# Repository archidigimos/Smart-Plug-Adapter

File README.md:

# Smart-Plug-Adapter
Converts any normal power outlet into smart power outlet when plugged into it. WiFi enabled, can be controlled through Android application or Web Application.

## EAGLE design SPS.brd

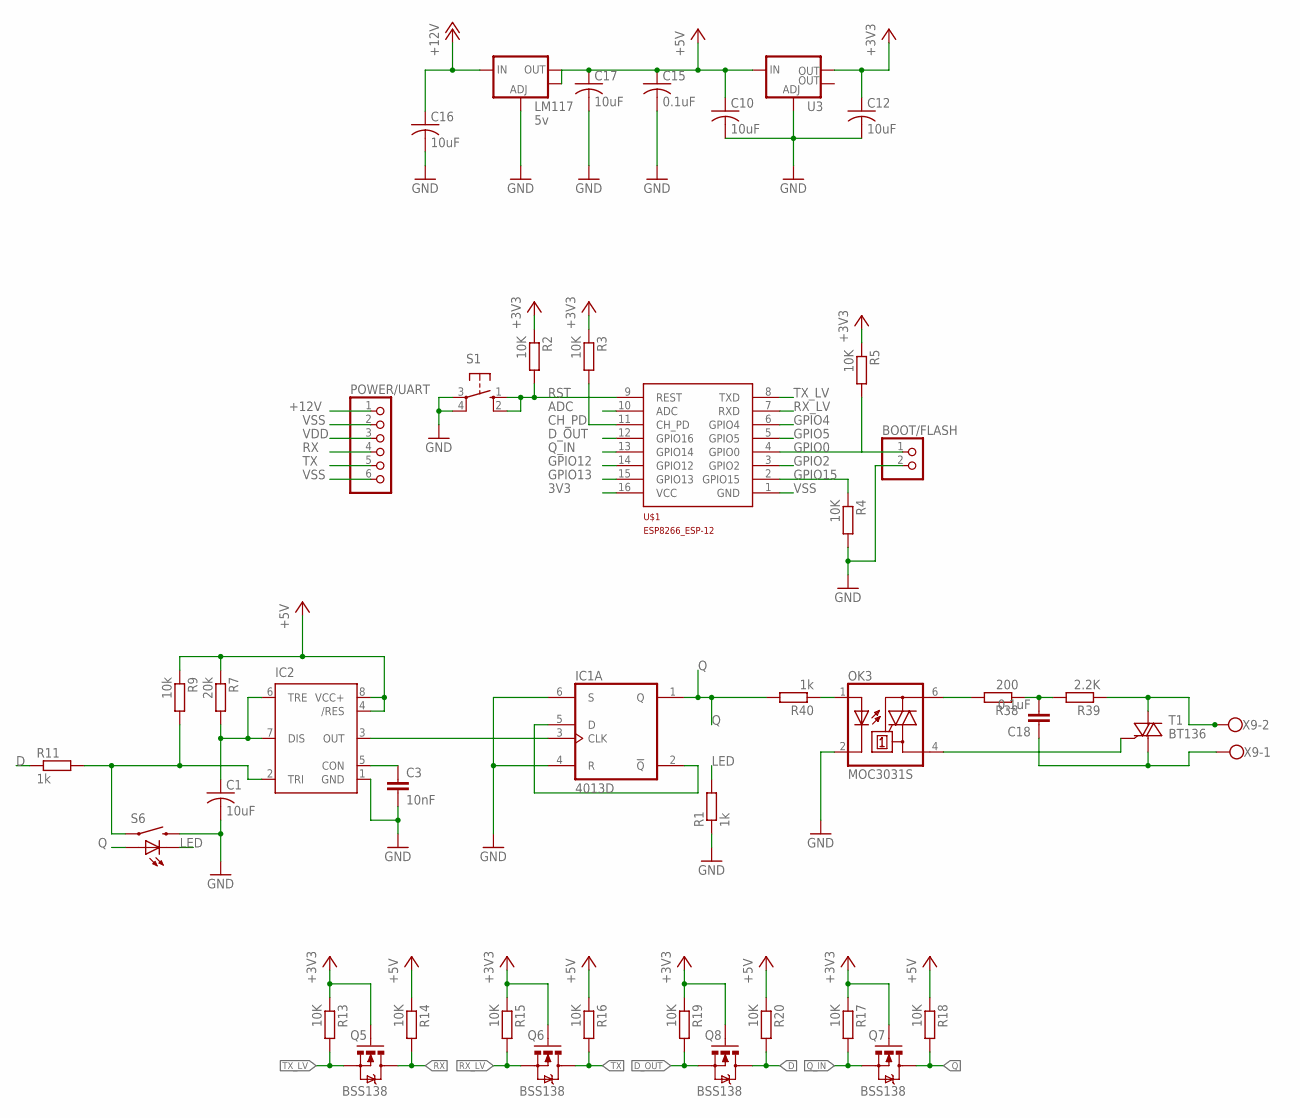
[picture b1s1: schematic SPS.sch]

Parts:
BOOT/FLASH: PINHD-1X2; 1X02
C1, C10, C12: 10uF; C1206
C3: 10nF; C1206
C15: 0.1uF; C0805
C16, C17: 10uF; C0805
C18: 0.1uF; C050-050X075
IC1: 4013D; SO14
IC2: NE555D; SO08
LM117: 5v; SOT223
OK3: MOC3031S; DIL6-SMD
POWER/UART: PINHD-1X6; 1X06
Q5, Q6, Q7, Q8: BSS138; SOT23-3
R1, R11, R40: 1k; R1206
R2, R3, R4, R5, R13, R14, R15, R16, R17, R18, R19, R20: 10K; R1206
R7: 20k; R1206
R9: 10k; R1206
R38: 200; 0414/15
R39: 2.2K; 0414/15
S1: 10-XX; B3F-10XX
S6: SWITCH-MOMENTARY-LEDPTH; TACTILE-PTH-LED-12MM
T1: BT136; TO220AB
U3: V_REG_LM1117SOT223; SOT223
U$1: ESP8266_ESP-12; ESP8266-ESP12
X9: W237-102

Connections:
3V3: C12.1, Q5.1 (G), Q6.1 (G), Q7.1 (G), Q8.1 (G), R2.1, R3.1, R5.1, R13.1, R15.1, R17.1, R19.1, U3.2 (OUT), U$1.16 (VCC)
+12V: C16.1, LM117.3 (IN), POWER/UART.1
ADC: U$1.10 (ADC)
CH_PD: R3.2, U$1.11 (CH_PD)
D: Q8.3 (D), R11.1, R20.2
D_OUT: Q8.2 (S), R19.2, U$1.12 (GPIO16)
GPIO0: BOOT/FLASH.1, R5.2, U$1.4 (GPIO0)
GPIO2: U$1.3 (GPIO2)
GPIO4: U$1.6 (GPIO4)
GPIO5: U$1.5 (GPIO5)
GPIO12: U$1.14 (GPIO12)
GPIO13: U$1.15 (GPIO13)
GPIO15: R4.1, U$1.2 (GPIO15)
LED: R1.2, S6.C
unnamed: OK3.6 (A2), R38.2
unnamed: C18.1, T1.1 (A1), X9.1
unnamed: IC1.2 (!Q), IC1.5 (D)
unnamed: IC1.3 (CLK), IC2.3 (OUT)
unnamed: C1.1, IC2.6 (TRE), IC2.7 (DIS), R7.2
unnamed: C3.1, IC2.5 (CON)
unnamed: IC2.2 (TRI), R9.2, R11.2, S6.4 (1)
unnamed: R39.1, T1.2 (A2), X9.2
unnamed: OK3.4 (A1), T1.3 (G)
unnamed: C18.2, R38.1, R39.2
unnamed: OK3.1 (A), R40.1
Q: IC1.1 (Q), Q7.3 (D), R18.2, R40.2, S6.A
Q_IN: Q7.2 (S), R17.2, U$1.13 (GPIO14)
RST: R2.2, S1.1 (S), S1.2 (S1), U$1.9 (REST)
RX: POWER/UART.4, Q5.3 (D), R14.2
RX_LV: Q6.2 (S), R15.2, U$1.7 (RXD)
TX: POWER/UART.5, Q6.3 (D), R16.2
TX_LV: Q5.2 (S), R13.2, U$1.8 (TXD)
VDD: C10.1, C15.1, C17.1, IC1.14 (VDD), IC2.4 (/RES), IC2.8 (VCC+), LM117.2 (OUT), LM117.4 (OUT), POWER/UART.3, R7.1, R9.1, R14.1, R16.1, R18.1, R20.1, U3.3 (IN)
VSS: BOOT/FLASH.2, C1.2, C3.2, C10.2, C12.2, C15.2, C16.2, C17.2, IC1.4 (R), IC1.6 (S), IC1.7 (VSS), IC2.1 (GND), LM117.1 (ADJ), OK3.2 (C), POWER/UART.2, POWER/UART.6, R1.1, R4.2, S1.3, S1.4 (P1), S6.2, U3.1 (ADJ), U$1.1 (GND)

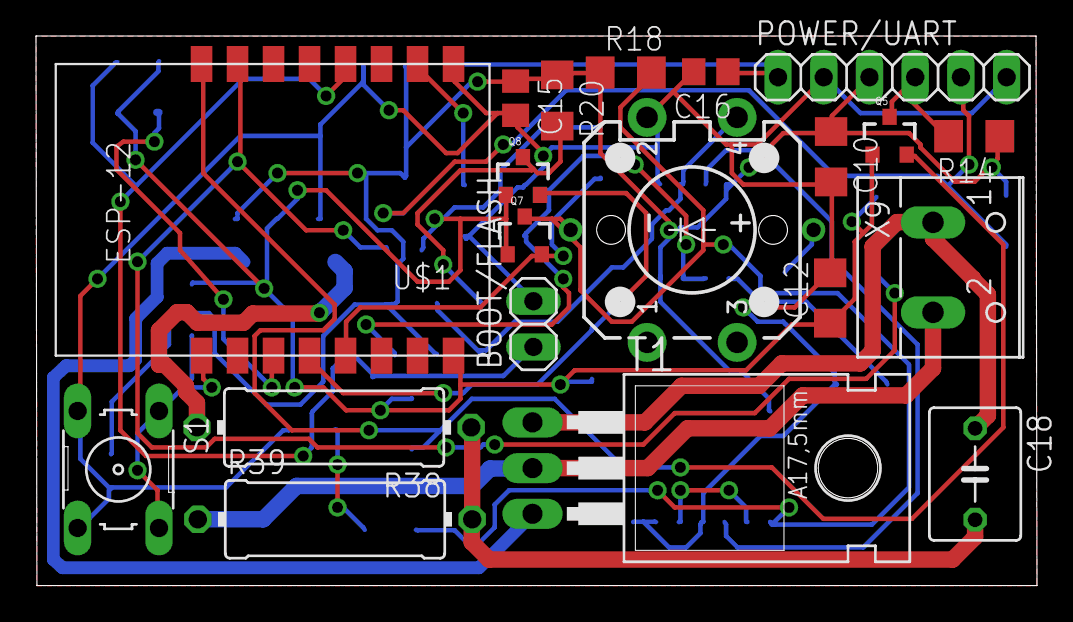
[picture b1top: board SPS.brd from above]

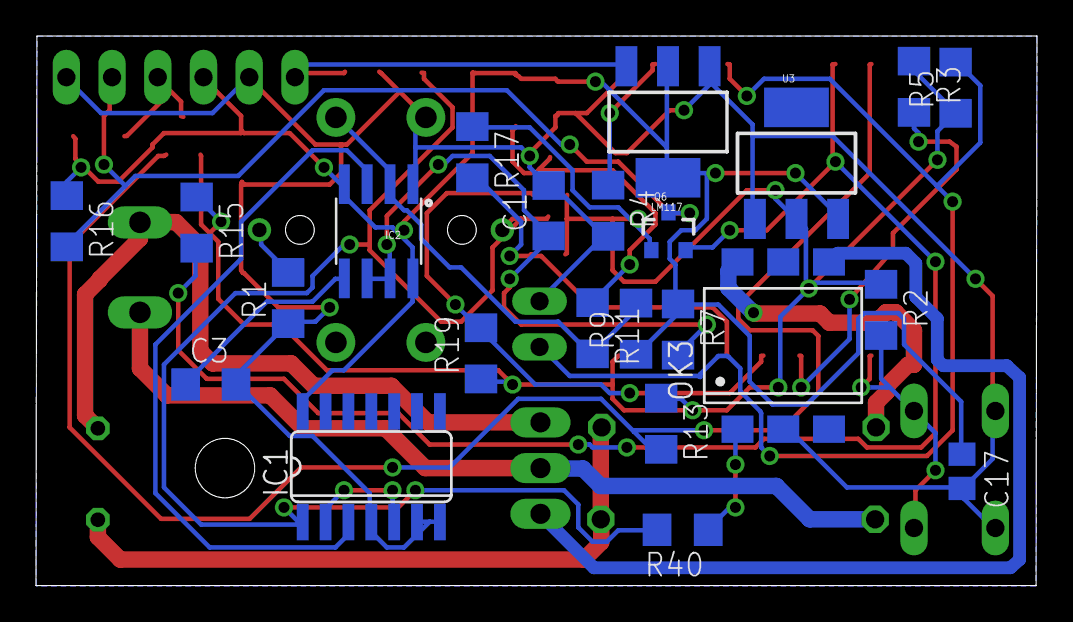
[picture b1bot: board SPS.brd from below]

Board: 2 copper layers, 55.6 x 30.5 mm, 43 parts (23 on the bottom side), 28 nets.

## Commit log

2017-08-08 :circus_tent: Added .gitattributes & .gitignore files
2017-08-08 Screenshot

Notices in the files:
parts and their libraries:
SparkFun-AnalogIC: Licensing:Creative Commons ShareAlike 4.0 International - https://creativecommons.org/licenses/by-sa/4.0
